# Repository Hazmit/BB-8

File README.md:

# BB-8
BB-8 Public Repository for parts and systems

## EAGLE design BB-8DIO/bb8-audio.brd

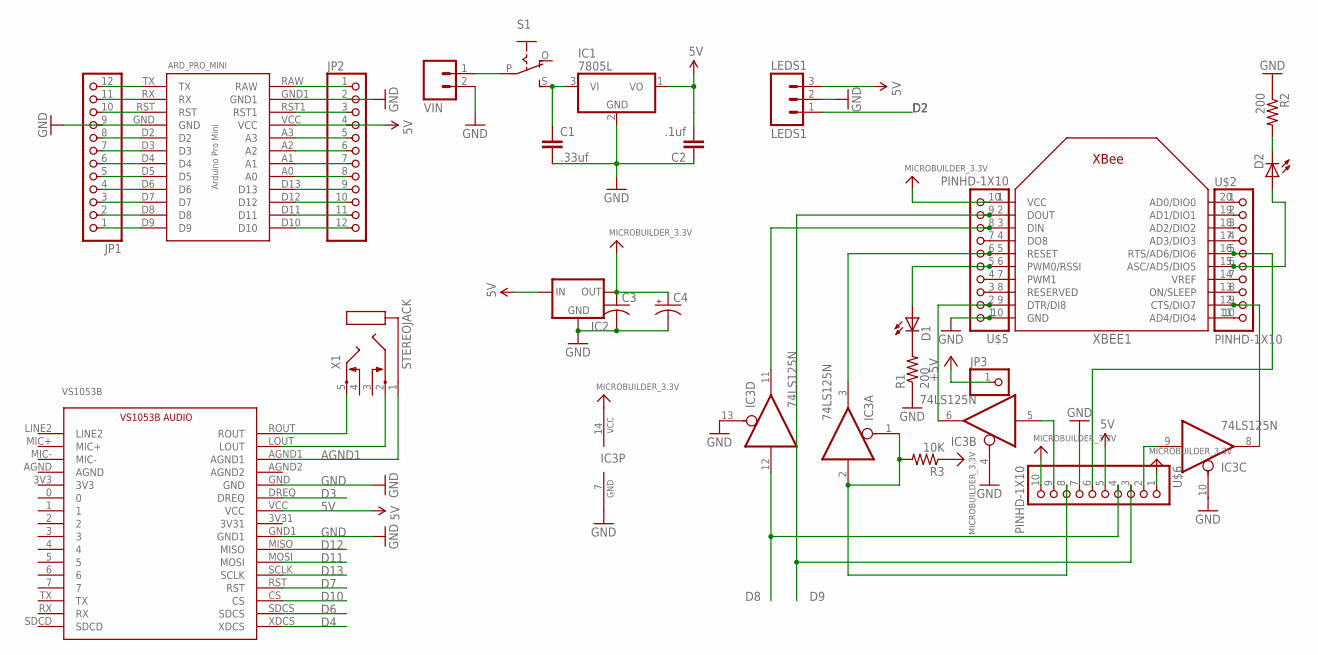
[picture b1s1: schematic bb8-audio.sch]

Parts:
ARD_PRO_MINI: ARD_PRO_MINI
C1: .33uf; CAP-PTH-SMALLEZ
C2: .1uf; CAP-PTH-SMALLEZ
C3: C-US025-025X050; C025-025X050
C4: CPOL-USE2.5-5; E2,5-5
D1, D2: LED3MM
IC1: 7805L; TO92
IC2: MC1700; TO92
IC3: 74LS125N; DIL14
JP1, JP2: PINHD-1X12-CB; 1X12-CB
JP3: PINHD-1X1; 1X01
LEDS1: LEDS1; 1X03
R1, R2: 200; 0207/10
R3: 10K; 0207/10
S1: EG1218S; EG1218
U$2, U$5, U$6: PINHD-1X10; 1X10-BIG
VIN: M02PTH; 1X02
VS1053B: VS1053B_BREAKOUT; VS1053_BREAKOUT
X1: STEREOJACK; STX3100
XBEE1: XBEE

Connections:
3.3V: C3.1, C4.+, IC2.3 (OUT), IC3.14 (VCC), R3.1, U$5.10, U$6.1, U$6.10, XBEE1.1 (VCC)
5V: ARD_PRO_MINI.VCC, C2.2, IC1.1 (VO), IC2.2 (IN), JP2.4, LEDS1.3, U$6.5, VS1053B.VCC
+5V: JP3.1
A0: ARD_PRO_MINI.A0, JP2.8
A1: ARD_PRO_MINI.A1, JP2.7
A2: ARD_PRO_MINI.A2, JP2.6
A3: ARD_PRO_MINI.A3, JP2.5
AGND1: VS1053B.AGND1, X1.1
D2: ARD_PRO_MINI.D2, JP1.8, LEDS1.1
D3: ARD_PRO_MINI.D3, JP1.7, VS1053B.DREQ
D4: ARD_PRO_MINI.D4, JP1.6, VS1053B.XDCS
D5: ARD_PRO_MINI.D5, JP1.5
D6: ARD_PRO_MINI.D6, JP1.4, VS1053B.SDCS
D7: ARD_PRO_MINI.D7, JP1.3, VS1053B.RST
D8: ARD_PRO_MINI.D8, IC3.12 (I), JP1.2, U$6.4
D9: ARD_PRO_MINI.D9, JP1.1, U$5.9, U$6.3, XBEE1.2 (DOUT)
D10: ARD_PRO_MINI.D10, JP2.12, VS1053B.CS
D11: ARD_PRO_MINI.D11, JP2.11, VS1053B.MOSI
D12: ARD_PRO_MINI.D12, JP2.10, VS1053B.MISO
D13: ARD_PRO_MINI.D13, JP2.9, VS1053B.SCLK
GND: ARD_PRO_MINI.GND, ARD_PRO_MINI.GND1, C1.2, C2.1, C3.2, C4.-, IC1.2 (GND), IC2.1 (GND), IC3.4 (OE), IC3.7 (GND), IC3.10 (OE), IC3.13 (OE), JP1.9, JP2.2, LEDS1.2, R1.1, R2.1, U$5.1, U$6.7, VIN.2, VS1053B.GND, VS1053B.GND1, XBEE1.10 (GND)
unnamed: C1.1, IC1.3 (VI), S1.S
unnamed: IC3.11 (O), U$5.8, XBEE1.3 (DIN)
unnamed: IC3.8 (O), U$2.9, XBEE1.12 (CTS/DIO7)
unnamed: U$5.7, XBEE1.4 (DO8)
unnamed: D1.A, U$5.5, XBEE1.6 (PWM0/RSSI)
unnamed: D1.K (C), R1.2
unnamed: D2.K (C), R2.2
unnamed: D2.A, U$2.6, XBEE1.15 (ASC/AD5/DIO5)
unnamed: IC3.6 (O), U$5.2, XBEE1.9 (DTR/DI8)
unnamed: U$5.3, XBEE1.8 (RESERVED)
unnamed: U$5.4, XBEE1.7 (PWM1)
unnamed: U$2.1, XBEE1.20 (AD0/DIO0)
unnamed: U$2.2, XBEE1.19 (AD1/DIO1)
unnamed: U$2.3, XBEE1.18 (AD2/DIO2)
unnamed: U$2.4, XBEE1.17 (AD3/DIO3)
unnamed: U$2.7, XBEE1.14 (VREF)
unnamed: U$2.8, XBEE1.13 (ON/SLEEP)
unnamed: U$2.10, XBEE1.11 (AD4/DIO4)
unnamed: VS1053B.LOUT, X1.2
unnamed: IC3.9 (I), U$6.2
unnamed: IC3.3 (O), U$5.6, XBEE1.5 (RESET)
unnamed: IC3.5 (I), U$6.9
unnamed: VS1053B.ROUT, X1.5
unnamed: S1.P, VIN.1
RAW: ARD_PRO_MINI.RAW, JP2.1
RESET: IC3.1 (OE), IC3.2 (I), R3.2, U$6.8
RST: ARD_PRO_MINI.RST, ARD_PRO_MINI.RST1, JP1.10, JP2.3
RTS1: U$2.5, U$6.6, XBEE1.16 (RTS/AD6/DIO6)
RX: ARD_PRO_MINI.RX, JP1.11
TX: ARD_PRO_MINI.TX, JP1.12

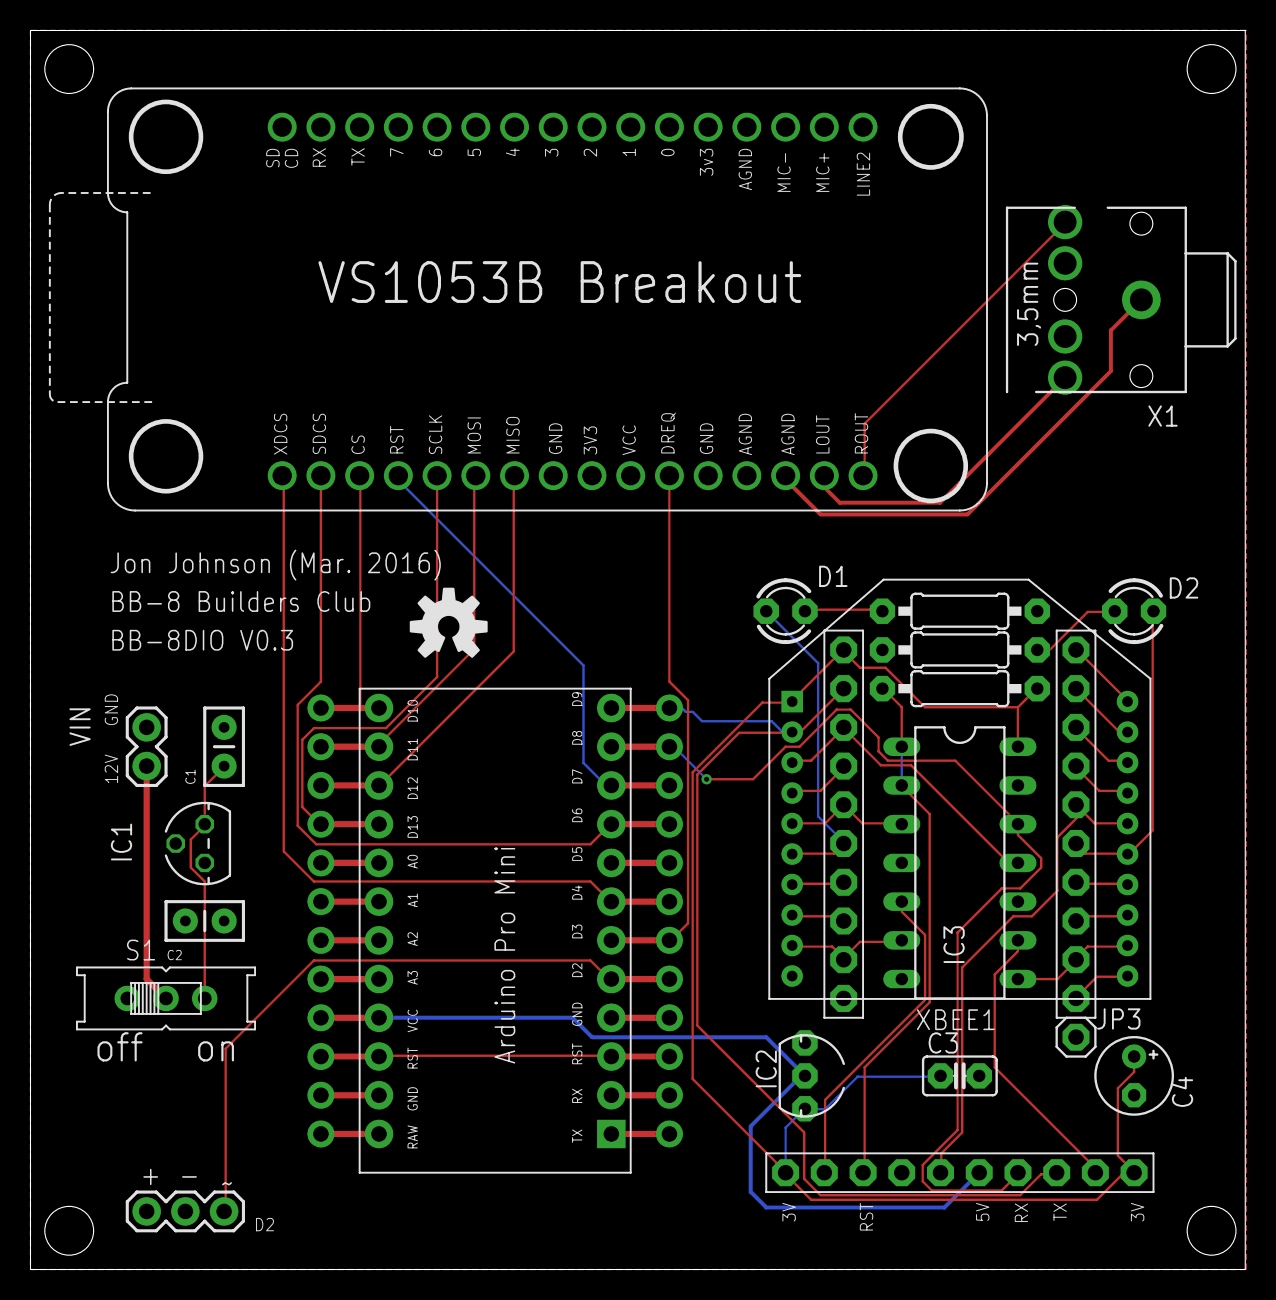
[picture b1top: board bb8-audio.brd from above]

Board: 2 copper layers, 79.7 x 81.3 mm, 26 parts (0 on the bottom side), 50 nets.

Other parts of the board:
U$3: OSHW-LOGO-M

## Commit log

2016-02-29 Initial Commit
    Initial Commit of files to the repository from Ed's work. I’ve also
    added my modified sphere light code.
2016-03-02 First commit of BB8-DIO
    This is the first commit of the BB8-DIO board to the repo. This is V0.2
    of the board.
2016-03-02 Ignoring lock files from eagle.
    Ignoring lock files from eagle.
2016-03-12 Adding updated files in sketchup
    Resized holes of slots to be 6.2mm to fit 1/4” plate. Also moved drill
    holes down so they could be sandwiched instead of needing to be tapped.
2016-03-12 Sphere lights updated (Work in progress)
    The status of the sphere lights is a bit of a work in progress. I’m
    doing work to update the communication to support serial input so you
    can debug from a computer. This will also be used later when
    programming actions from a computer app.
2016-03-12 Revision 0.3 of the BB-8DIO board.
    Adding revision 0.3. This has the audio breakout board footprint so the
    breakout can be dropped on using header pins. This also has reworked a
    lot of other pins and headers have been removed because they are no
    longer available after adding the audio breakout. Resolved some
    silkscreen issues and also resolved issues with 5V on arduino input and
    Xbee input.
2016-03-12 Adding customer libraries used in board and schematic.

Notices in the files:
parts and their libraries:
SparkFun-Connectors: Licensing: CC v3.0 Share-Alike You are welcome to use this library for commercial purposes.
